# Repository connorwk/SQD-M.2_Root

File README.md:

# SQD-M.2_Root
Breakout from M.2 to a PCIe root port designed for the SQRL Acorn FPGA boards.

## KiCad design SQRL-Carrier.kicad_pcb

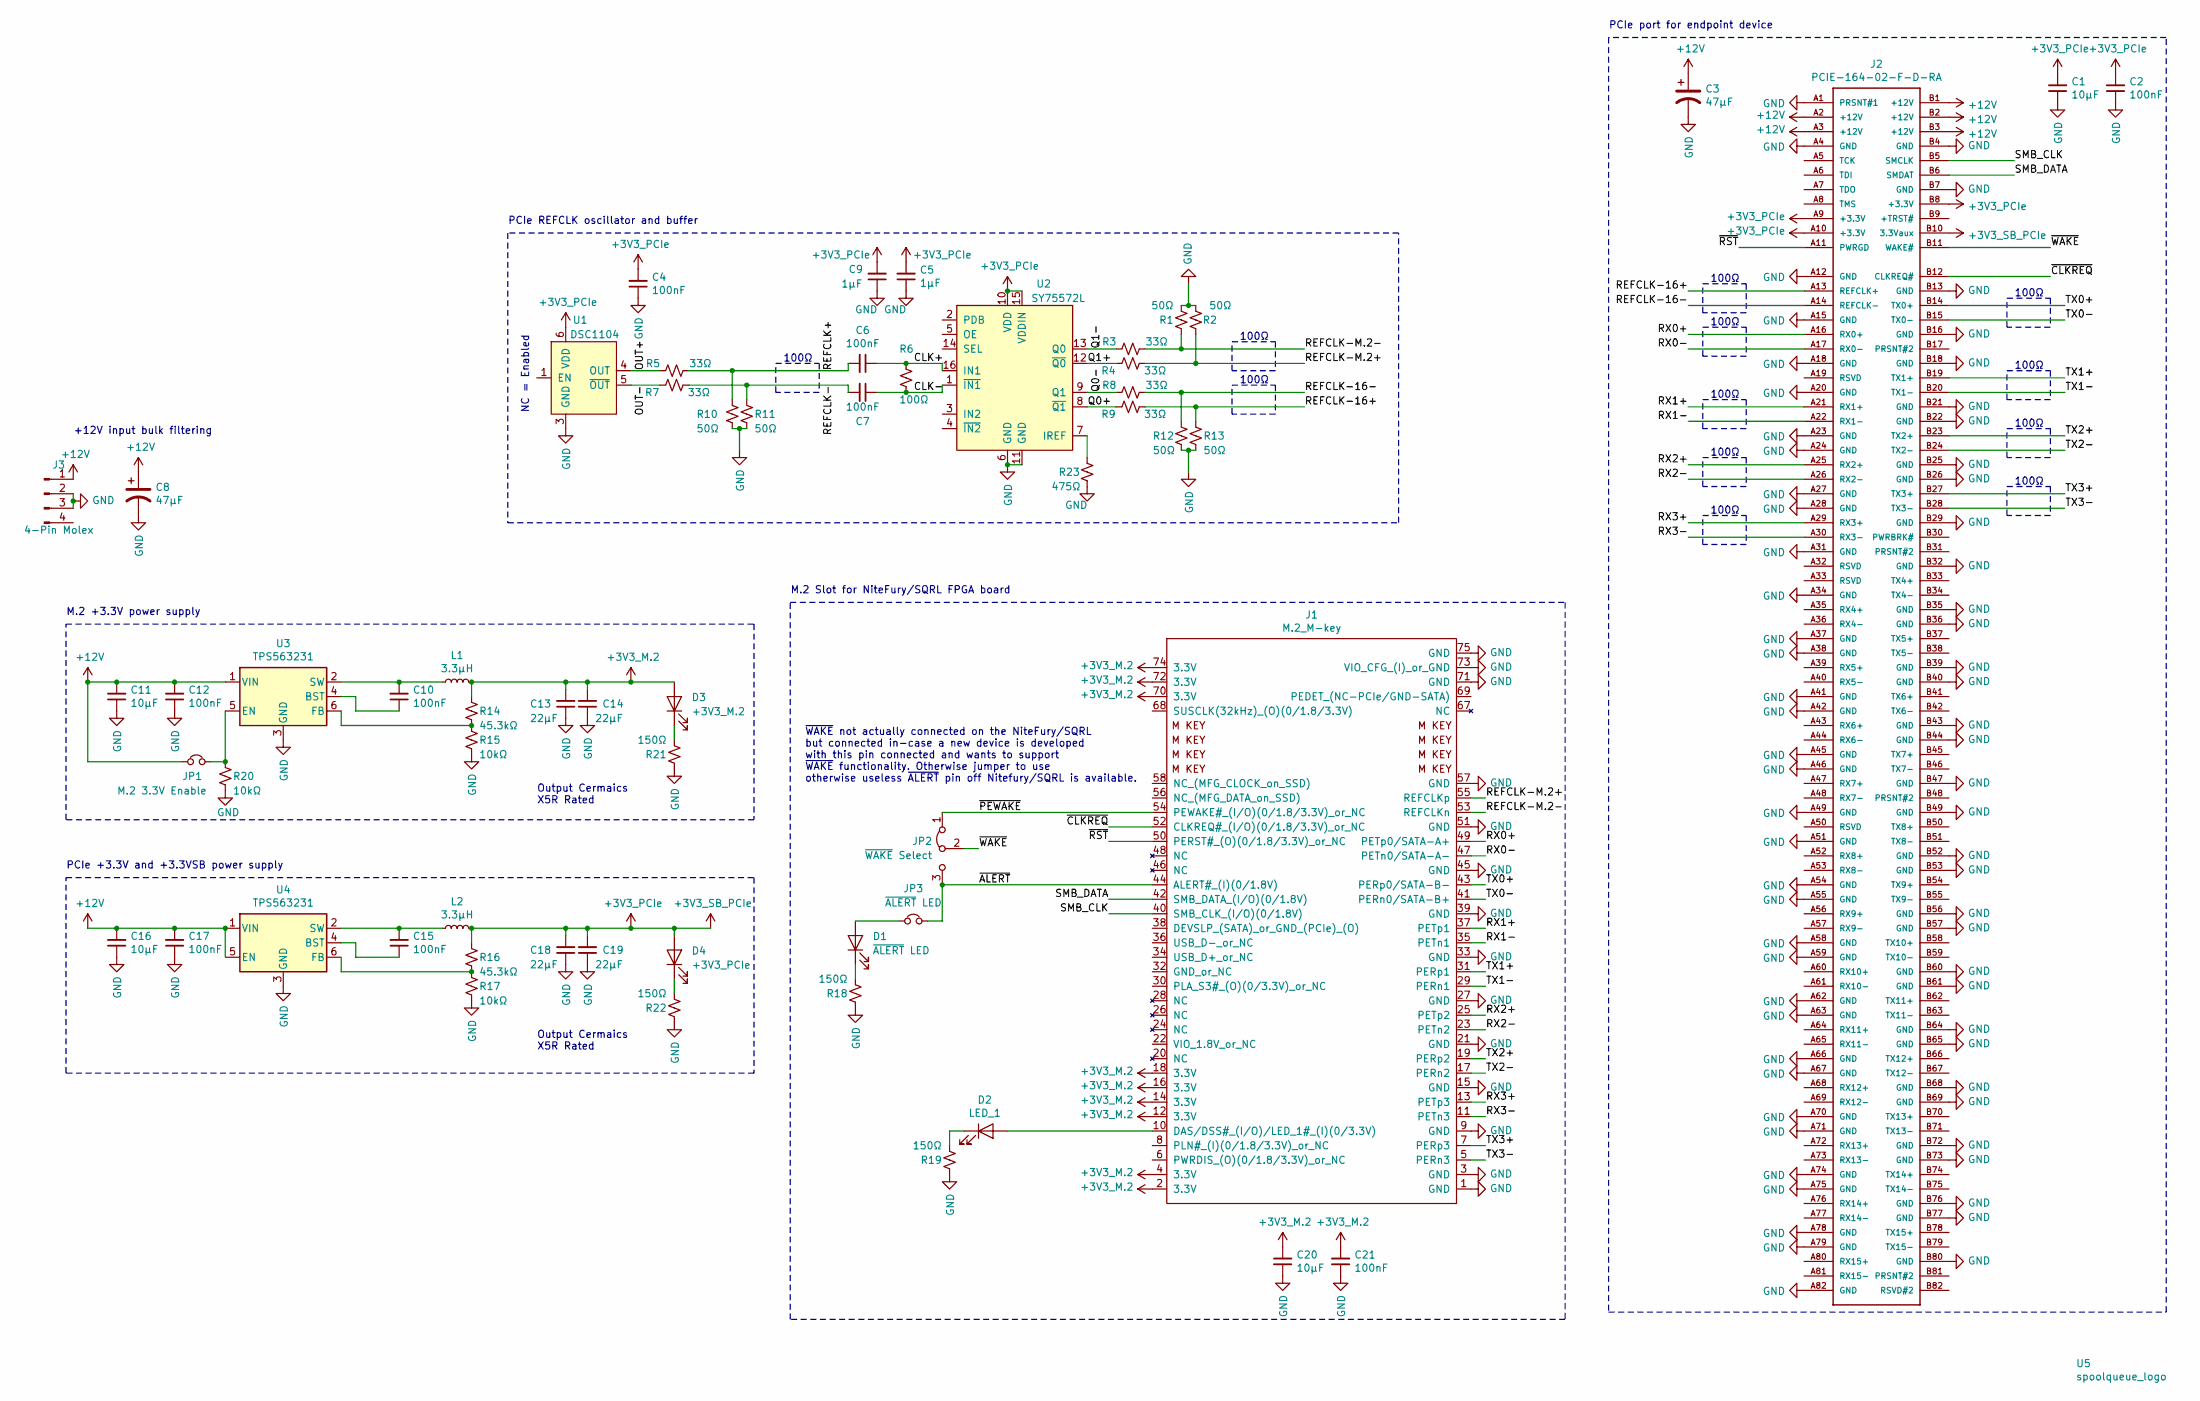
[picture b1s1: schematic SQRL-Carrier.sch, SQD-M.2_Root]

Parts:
C1, C11, C16, C20: 10μF; C_1206_3216Metric
C2, C4, C6, C7, C10, C12, C15, C17, C21: 100nF; C_0402_1005Metric
C3, C8: 47μF; CP_Radial_D6.3mm_P2.50mm
C5, C9: 1μF; C_0402_1005Metric
C13, C14, C18, C19: 22μF; C_0805_2012Metric
D1: ~ALERT~ LED; LED_PLCC-2
D2: LED_1; LED_PLCC-2
D3: +3V3_M.2; LED_PLCC-2
D4: +3V3_PCIe; LED_PLCC-2
J1: M.2_M-key; Conn_TE-M.2-0.5-67P-M-key-doublesided
J2: PCIE-164-02-F-D-RA
J3: 4-Pin Molex; AMP-4POS-(MOLEX)-RA
JP1: M.2 3.3V Enable; PinHeader_1x02_P2.54mm_Vertical
JP2: ~WAKE~ Select; PinHeader_1x03_P2.54mm_Vertical
JP3: ~ALERT~ LED; PinHeader_1x02_P2.54mm_Vertical
L1, L2: 3.3μH; L_Taiyo-Yuden_NR-50xx
R1, R2, R10, R11, R12, R13: 50Ω; R_0402_1005Metric
R3, R4, R5, R7, R8, R9: 33Ω; R_0402_1005Metric
R6: 100Ω; R_0402_1005Metric
R14, R16: 45.3kΩ; R_0402_1005Metric
R15, R17, R20: 10kΩ; R_0402_1005Metric
R18, R19, R21, R22: 150Ω; R_0402_1005Metric
R23: 475Ω; R_0402_1005Metric
U1: DSC1104; CDFN-6pin-5x3.2mm
U2: SY75572L; VQFN-16-1EP_3x3mm_P0.5mm_EP1.45x1.45mm
U3, U4: TPS563231; SOT-563
U5: spoolqueue_logo; spoolqueue_logo_small

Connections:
+3V3_M.2: C13.2, C14.2, C20.2, C21.2, D3.2 (A), J1.2 (3.3V), J1.4 (3.3V), J1.12 (3.3V), J1.14 (3.3V), J1.16 (3.3V), J1.18 (3.3V), J1.70 (3.3V), J1.72 (3.3V), J1.74 (3.3V), L1.2, R14.1
+3V3_PCIe: C1.2, C2.2, C4.2, C5.2, C9.2, C18.2, C19.2, D4.2 (A), J2.A9 (+3.3V), J2.A10 (+3.3V), J2.B8 (+3.3V), J2.B10 (3.3Vaux), L2.2, R16.1, U1.6 (VDD), U2.10 (VDD), U2.15 (VDDIN)
+12V: C3.1, C8.1, C11.2, C12.2, C16.2, C17.2, J2.A2 (+12V), J2.A3 (+12V), J2.B1 (+12V), J2.B2 (+12V), J2.B3 (+12V), J3.1, JP1.1, U3.1 (VIN), U4.1 (VIN), U4.5 (EN)
/CLK+: C6.1, R6.1, U2.16 (IN1)
/CLK-: C7.1, R6.2, U2.1 (~IN1~)
/OUT+: R5.2, U1.4 (OUT)
/OUT-: R7.1, U1.5 (~OUT~)
/Q0+: R9.1, U2.8 (~Q1~)
/Q0-: R8.2, U2.9 (Q1)
/Q1+: R4.1, U2.12 (~Q0~)
/Q1-: R3.2, U2.13 (Q0)
/REFCLK+: C6.2, R5.1, R10.1
/REFCLK-: C7.2, R7.2, R11.1
/REFCLK-16+: J2.A13 (REFCLK+), R9.2, R13.1
/REFCLK-16-: J2.A14 (REFCLK-), R8.1, R12.1
/REFCLK-M.2+: J1.55 (REFCLKp), R2.1, R4.2
/REFCLK-M.2-: J1.53 (REFCLKn), R1.1, R3.1
/RX0+: J1.49 (PETp0/SATA-A+), J2.A16 (RX0+)
/RX0-: J1.47 (PETn0/SATA-A-), J2.A17 (RX0-)
/RX1+: J1.37 (PETp1), J2.A21 (RX1+)
/RX1-: J1.35 (PETn1), J2.A22 (RX1-)
/RX2+: J1.25 (PETp2), J2.A25 (RX2+)
/RX2-: J1.23 (PETn2), J2.A26 (RX2-)
/RX3+: J1.13 (PETp3), J2.A29 (RX3+)
/RX3-: J1.11 (PETn3), J2.A30 (RX3-)
/SMB_CLK: J1.40 (SMB_CLK_(I/O)(0/1.8V)), J2.B5 (SMCLK)
/SMB_DATA: J1.42 (SMB_DATA_(I/O)(0/1.8V)), J2.B6 (SMDAT)
/TX0+: J1.43 (PERp0/SATA-B-), J2.B14 (TX0+)
/TX0-: J1.41 (PERn0/SATA-B+), J2.B15 (TX0-)
/TX1+: J1.31 (PERp1), J2.B19 (TX1+)
/TX1-: J1.29 (PERn1), J2.B20 (TX1-)
/TX2+: J1.19 (PERp2), J2.B23 (TX2+)
/TX2-: J1.17 (PERn2), J2.B24 (TX2-)
/TX3+: J1.7 (PERp3), J2.B27 (TX3+)
/TX3-: J1.5 (PERn3), J2.B28 (TX3-)
/~ALERT~: J1.44 (ALERT#_(I)(0/1.8V)), JP2.3 (B), JP3.2
/~CLKREQ~: J1.52 (CLKREQ#_(I/O)(0/1.8/3.3V)_or_NC), J2.B12 (CLKREQ#)
/~PEWAKE~: J1.54 (PEWAKE#_(I/O)(0/1.8/3.3V)_or_NC), JP2.1 (A)
/~RST~: J1.50 (PERST#_(O)(0/1.8/3.3V)_or_NC), J2.A11 (PWRGD)
/~WAKE~: J2.B11 (WAKE#), JP2.2 (C)
GND: C1.1, C2.1, C3.2, C4.1, C5.1, C8.2, C9.1, C11.1, C12.1, C13.1, C14.1, C16.1, C17.1, C18.1, C19.1, C20.1, C21.1, J1.1 (GND), J1.3 (GND), J1.9 (GND), J1.15 (GND), J1.21 (GND), J1.27 (GND), J1.33 (GND), J1.39 (GND), J1.45 (GND), J1.51 (GND), J1.57 (GND), J1.71 (GND), J1.73 (VIO_CFG_(I)_or_GND), J1.75 (GND), J2.A1 (PRSNT#1), J2.A4 (GND), J2.A12 (GND), J2.A15 (GND), J2.A18 (GND), J2.A20 (GND), J2.A23 (GND), J2.A24 (GND), J2.A27 (GND), J2.A28 (GND), J2.A31 (GND), J2.A34 (GND), J2.A37 (GND), J2.A38 (GND), J2.A41 (GND), J2.A42 (GND), J2.A45 (GND), J2.A46 (GND), J2.A49 (GND), J2.A51 (GND), J2.A54 (GND), J2.A55 (GND), J2.A58 (GND), J2.A59 (GND), J2.A62 (GND), J2.A63 (GND), J2.A66 (GND), J2.A67 (GND), J2.A70 (GND), J2.A71 (GND), J2.A74 (GND), J2.A75 (GND), J2.A78 (GND), J2.A79 (GND), J2.A82 (GND), J2.B4 (GND), J2.B7 (GND), J2.B13 (GND), J2.B16 (GND), J2.B18 (GND), J2.B21 (GND), J2.B22 (GND), J2.B25 (GND), J2.B26 (GND), J2.B29 (GND), J2.B32 (GND), J2.B35 (GND), J2.B36 (GND), J2.B39 (GND), J2.B40 (GND), J2.B43 (GND), J2.B44 (GND), J2.B47 (GND), J2.B49 (GND), J2.B52 (GND), J2.B53 (GND), J2.B56 (GND), J2.B57 (GND), J2.B60 (GND), J2.B61 (GND), J2.B64 (GND), J2.B65 (GND), J2.B68 (GND), J2.B69 (GND), J2.B72 (GND), J2.B73 (GND), J2.B76 (GND), J2.B77 (GND), J2.B80 (GND), J3.2, J3.3, R1.2, R2.2, R10.2, R11.2, R12.2, R13.2, R15.2, R17.2, R18.1, R19.1, R20.2, R21.1, R22.1, R23.2, U1.3 (GND), U2.6 (GND), U2.11 (GND), U3.3 (GND), U4.3 (GND)
unnamed: C10.1, U3.4 (BST)
unnamed: C10.2, L1.1, U3.2 (SW)
unnamed: C15.1, U4.4 (BST)
unnamed: C15.2, L2.1, U4.2 (SW)
unnamed: D1.1 (K), R18.2
unnamed: D1.2 (A), JP3.1
unnamed: D2.1 (K), R19.2
unnamed: D2.2 (A), J1.10 (DAS/DSS#_(I/O)/LED_1#_(I)(0/3.3V))
unnamed: D3.1 (K), R21.2
unnamed: D4.1 (K), R22.2
unnamed: JP1.2, R20.1, U3.5 (EN)
unnamed: R14.2, R15.1, U3.6 (FB)
unnamed: R16.2, R17.1, U4.6 (FB)
unnamed: R23.1, U2.7 (IREF)

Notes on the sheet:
100Ω
~WAKE~ not actually connected on the NiteFury/SQRL but connected in-case a new device is developed with this pin connected and wants to support ~WAKE~ functionality. Otherwise jumper to use otherwise useless ~ALERT~ pin off Nitefury/SQRL is available.
M.2 +3.3V power supply
PCIe +3.3V and +3.3VSB power supply
+12V input bulk filtering
Output Cermaics X5R Rated
PCIe REFCLK oscillator and buffer
M.2 Slot for NiteFury/SQRL FPGA board
PCIe port for endpoint device
NC = Enabled

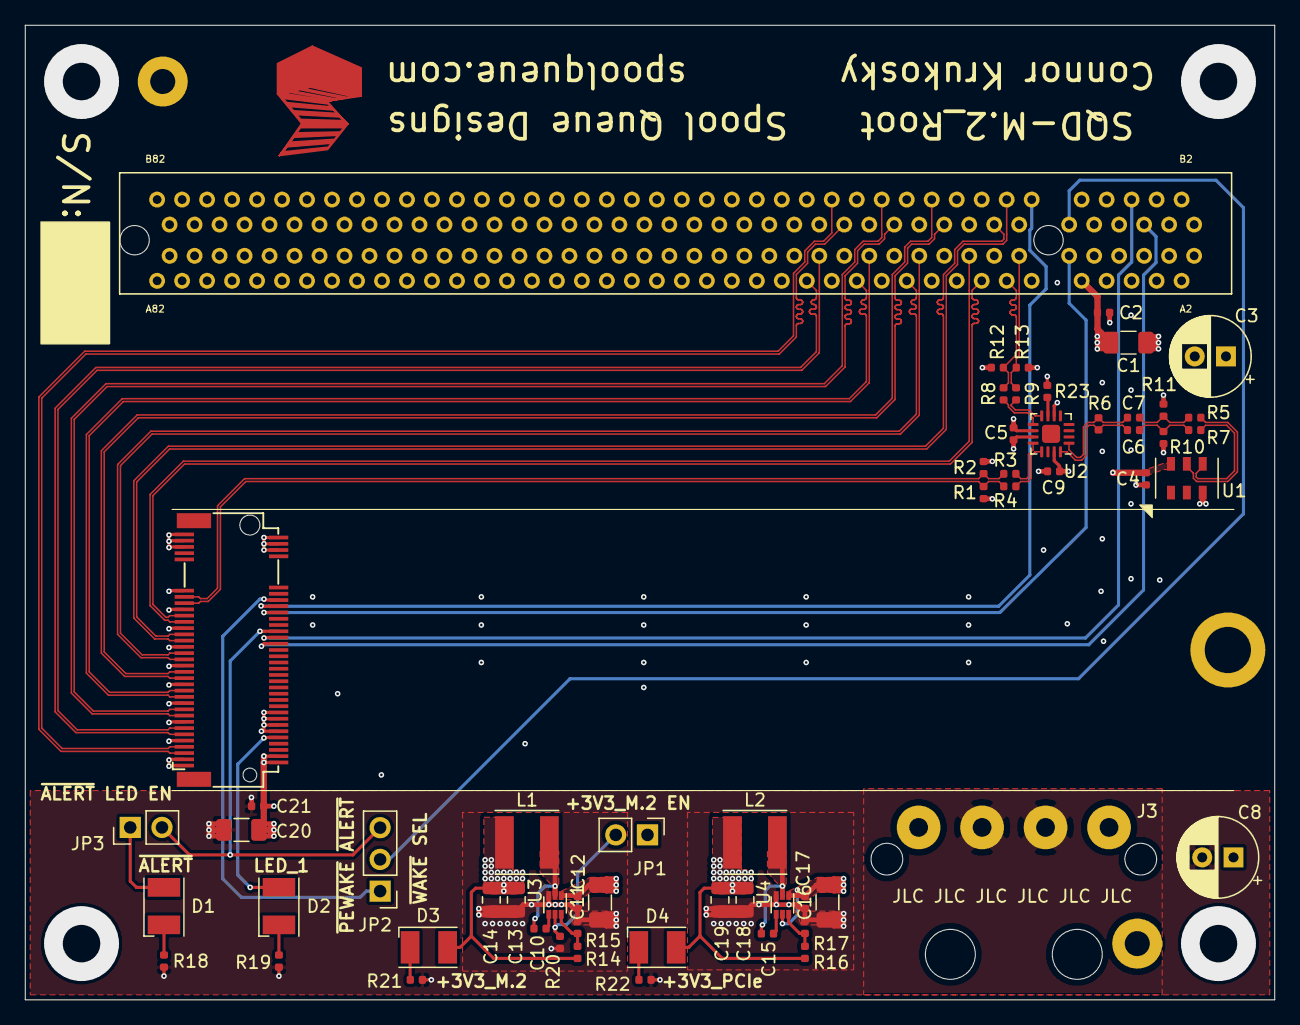
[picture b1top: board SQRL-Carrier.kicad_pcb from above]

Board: 4 copper layers, 100.0 x 78.0 mm, 61 parts (0 on the bottom side), 55 nets.

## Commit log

2020-08-26 Initial commit of hardware revision 1.0
2020-09-16 Cleanup of backup files and adding .gitignore to repository.
2020-09-16 Hardware revision 2
